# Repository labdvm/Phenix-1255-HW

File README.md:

<p align="center">
  <picture>
    <source media="(prefers-color-scheme: dark)" srcset="documentation/images/phenix-1255_logo_white.png">
    
  </picture>
</p>

<p align="center">
  <b>"Pi-less" SX1255 RF shield for the NXP FRDM-MCXN947</b><br>
  KiCad hardware design · separate RX/TX paths · 38.4 MHz TCXO · HS USB or Ethernet via the FRDM board
</p>

<p align="center">

</p>

<p align="center">
  <a href="#overview">Overview</a> ·
  <a href="#board-variants">Board variants</a> ·
  <a href="#features">Features</a> ·
  <a href="#preview">Preview</a> ·
  <a href="#documentation">Documentation</a> ·
  <a href="#repository-contents">Repository contents</a> ·
  <a href="#getting-started">Getting started</a> ·
  <a href="#license">License</a>
</p>

## Overview

Phenix-1255 is a shield board that pairs the popular **Semtech SX1255** RF transceiver with the
**NXP FRDM-MCXN947** development board — no Raspberry Pi required. The MCX N947 handles the
I/Q sample stream and talks to the host PC over **High-Speed USB** or **Ethernet**.

The project idea comes from **[DM5LF](https://github.com/w4tchd0g)**, who also writes the software. The hardware was designed by **[Z32IT](https://github.com/labdvm)**.

| | |
|---|---|
| 🧠 **Controller** | NXP FRDM-MCXN947 (plugs directly onto the shield headers) |
| 📡 **RF transceiver** | Semtech SX1255 (I/Q, 400–510 MHz) |
| ⏱️ **Reference clock** | 38.4 MHz TCXO, 0.5–1 ppm |
| 🔌 **Host link** | High-Speed USB 2.0 or Ethernet of the FRDM-MCXN947 |
| ⚡ **Power** | 5 V from the FRDM-MCXN947 (USB-C); PoE operation possible with a 48 V → 5 V USB-C PoE splitter |
| 📐 **PCB** | 118 × 55 mm, 2 layers, 1.2 mm thickness |

## Board variants

The repository contains two variants of revision V2. Both share the same board outline, headers,
power supply, user interface and RX path.

| Variant | Folder | Difference |
|---|---|---|
| **V2** | [`FRDM-SX1255/`](FRDM-SX1255) | SX1255 TX output → low-pass filter → U.FL |
| **V2 Plus** | [`FRDM-SX1255+/`](FRDM-SX1255+) | Additional **TX driver amplifier** (Qorvo TQP3M9036, U2) between the SX1255 and the low-pass filter, with a resistive π-attenuator (R29–R31) at its input. The amplifier runs from 5 V and is switched together with the PA via `~PA_EN`. |

## Features

- **Separate RX and TX paths** with U.FL connectors (*TX* J1, *RX* J2)
  - RX: SAW band-pass filter (Tai-Saw TA0655A, 430 MHz centre frequency, 2 MHz bandwidth) → LC matching → `RFI`
  - TX: `RFO_P` → low-pass filter (Mini-Circuits LFCN-490+) → U.FL; V2 Plus adds the TQP3M9036 driver amplifier
- **Switchable PA supply** – P-MOSFET (BSS84) controlled by `~PA_EN`, with a *bypass* solder jumper
- **Power supply** – resettable 500 mA fuse, TVS diode array (SP0502BAHT), ferrite bead and 3.3 V LDO (MCP1703)
- **User interface**
  - Three push buttons: *←*, *OK*, *→*
  - Socket for an I²C OLED display
  - Status LEDs: *PWR*, *Err*, *Warn*, *Good*

## Preview

### V2

| Top | Bottom |
|:---:|:---:|
|  |  |

### V2 Plus

| Top | Bottom |
|:---:|:---:|
|  |  |

The images are rendered from the `.kicad_pcb` files with the KiCad 3D renderer and show the fully
assembled board with a 0.96″ OLED module plugged into its socket, including the parts that are
marked *do not populate* in the layout (FRDM headers, OLED socket, SAW filter). After changing the
layout, run [`./scripts/render.sh`](scripts/render.sh) to update the images.

### 3D models

Every part on the board has a 3D model, so the board can be checked mechanically (e.g. for an
enclosure) and exported as STEP from KiCad. Most models come from the KiCad standard library
(`${KICAD10_3DMODEL_DIR}`); parts without a matching library model use these substitutes:

| Part | Footprint | 3D model | Source |
|---|---|---|---|
| FRDM headers J1, J2, J3, J4, J9, J12 | Samtec SSQ (FRDM template) | `PinHeader_2xNN_P2.54mm_Vertical` | KiCad library, mounted below the board |
| U.FL connectors *TX* / *RX* | `U.FL_Molex_MCRF_73412-0110_Vertical` | `U.FL_Hirose_U.FL-R-SMT-1_Vertical`, rotated 90° | KiCad library (no model for the Molex footprint) |
| Push buttons SW1–SW3 | `PTS647SK38SMTR2LFS` | `SW_SPST_PTS647Sx70` (7.0 mm actuator, as in the BOM) | KiCad library |
| SAW filter X1 (TA0655A) | `Filter_SAW-6_3.8x3.8mm` | [`3dmodels/TA0655A.stp`](FRDM-SX1255/3dmodels/TA0655A.stp) | Project file |
| TX amplifier U2 (V2 Plus) | `SON50P200X200X95-9N` | `VDFN-8-1EP_2x2mm_P0.5mm_EP0.9x1.7mm` | KiCad library |
| OLED display (plugged into J5) | `PinSocket_1x04_P2.54mm_Vertical` | [`3dmodels/OLED_0.96in_128x64_I2C.stp`](FRDM-SX1255/3dmodels/OLED_0.96in_128x64_I2C.stp) – 0.96″ 128×64 SSD1306 I²C module, as a second model on the socket | Project file |

Mounting holes and the *bypass* solder jumper need no model.

The shield is designed for the NXP FRDM-MCXN947 development board, see the
[NXP FRDM-MCXN947 product page](https://www.nxp.com/design/design-center/development-boards-and-designs/FRDM-MCXN947)
for photos, documentation and the board pinout.

## Documentation

| Document | Content |
|---|---|
| [Hardware](documentation/hardware.md) | Block overview, header pin assignment, PA supply and *bypass* jumper, power supply, V2 Plus amplifier |
| [Manufacturing and assembly](documentation/manufacturing.md) | PCB specification, production files, assembly notes, first power-up |

## Host PC requirements

| Component | Minimum |
|---|---|
| Interface | USB 2.0 (High-Speed) or Ethernet |
| CPU | Intel or AMD, 4 cores |
| RAM | 4 GB DDR3 |
| Storage | SSD |
| OS | Xubuntu x64 |

## Repository contents

Each board variant is a self-contained KiCad project in its own folder:

```
Phenix-1255-HW/
├── FRDM-SX1255/                      # V2
│   ├── FRDM-SX1255-V2.kicad_pro      # KiCad project – open this one
│   ├── FRDM-SX1255-V2.kicad_sch      # schematic
│   ├── FRDM-SX1255-V2.kicad_pcb      # PCB layout
│   ├── FRDM-SX1255-V2.pdf            # schematic as PDF
│   ├── FRDM-SX1255-V2.png / _b.png   # 2D board views (KiCad export)
│   ├── 3dmodels/                     # project-specific 3D models
│   └── Gerber and BOM/               # manufacturing data
│       ├── …_gerber.zip              # Gerber and drill files for PCB fabrication
│       ├── …_bom.csv                 # bill of materials (incl. DigiKey part numbers)
│       ├── …_positions.csv           # pick-and-place positions for assembly
│       └── …_netlist.ipc             # IPC-D-356 netlist for electrical testing
├── FRDM-SX1255+/                     # V2 Plus – same structure, files named "FRDM-SX1255+ V2.*"
├── documentation/                    # hardware and manufacturing documentation, images
└── scripts/render.sh                 # renders the PCB images (needs kicad-cli)
```

| Quick links | V2 | V2 Plus |
|---|---|---|
| Schematic (PDF) | [`FRDM-SX1255-V2.pdf`](FRDM-SX1255/FRDM-SX1255-V2.pdf) | [`FRDM-SX1255+ V2.pdf`](FRDM-SX1255+/FRDM-SX1255+%20V2.pdf) |
| Gerber | [`…_gerber.zip`](FRDM-SX1255/Gerber%20and%20BOM/FRDM-SX1255-V2.kicad_pcb_gerber.zip) | [`…_gerber.zip`](FRDM-SX1255+/Gerber%20and%20BOM/FRDM-SX1255+%20V2.kicad_pcb_gerber.zip) |
| BOM | [`…_bom.csv`](FRDM-SX1255/Gerber%20and%20BOM/FRDM-SX1255-V2.kicad_pcb_bom.csv) | [`…_bom.csv`](FRDM-SX1255+/Gerber%20and%20BOM/FRDM-SX1255+%20V2.kicad_pcb_bom.csv) |
| Positions | [`…_positions.csv`](FRDM-SX1255/Gerber%20and%20BOM/FRDM-SX1255-V2.kicad_pcb_positions.csv) | [`…_positions.csv`](FRDM-SX1255+/Gerber%20and%20BOM/FRDM-SX1255+%20V2.kicad_pcb_positions.csv) |

## Getting started

1. **Choose a variant** – V2, or V2 Plus if you want the additional TX driver amplifier.
2. **Order the PCB** – upload the Gerber ZIP to a PCB manufacturer of your choice
   (2 layers, **1.2 mm** board thickness). For assembly, provide the BOM and position files as well.
   Details: [Manufacturing and assembly](documentation/manufacturing.md).
3. **Assemble** the shield and plug it onto the FRDM-MCXN947.
4. **Connect antennas / RF cabling** to the U.FL connectors *TX* (J1) and *RX* (J2).
5. **Install the software** from [phenix-1255-sw](https://github.com/w4tchd0g/phenix-1255-sw).

## Related projects

- 💻 **Software:** [w4tchd0g/phenix-1255-sw](https://github.com/w4tchd0g/phenix-1255-sw)

## Credits

- **Idea & software:** DM5LF – [@w4tchd0g](https://github.com/w4tchd0g)
- **Hardware design:** Z32IT – [@labdvm](https://github.com/labdvm)

## License

Copyright © Z32IT 2026.

This source describes Open Hardware and is licensed under the **CERN-OHL-P v2**.

You may redistribute and modify this source and make products using it under the terms of the
[CERN-OHL-P v2](https://ohwr.org/cern_ohl_p_v2.txt). This source is distributed **WITHOUT ANY EXPRESS
OR IMPLIED WARRANTY, INCLUDING OF MERCHANTABILITY, SATISFACTORY QUALITY AND FITNESS FOR A PARTICULAR
PURPOSE**. Please see the CERN-OHL-P v2 for applicable conditions.

Source location: <https://github.com/labdvm/Phenix-1255-HW>

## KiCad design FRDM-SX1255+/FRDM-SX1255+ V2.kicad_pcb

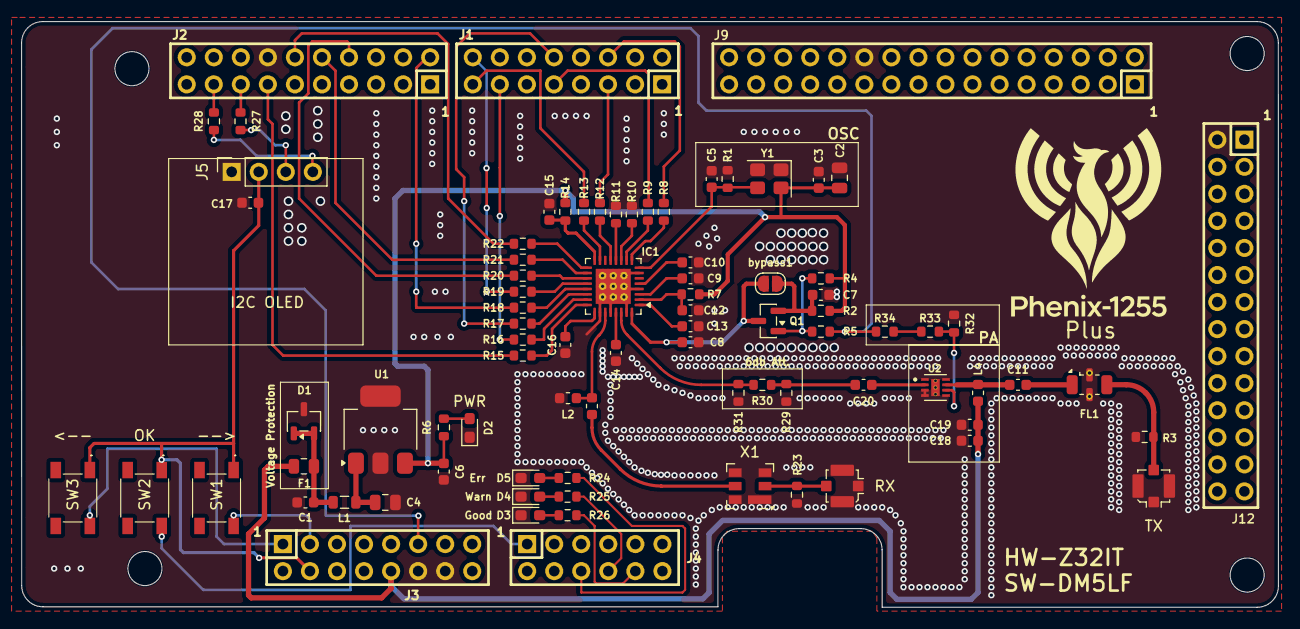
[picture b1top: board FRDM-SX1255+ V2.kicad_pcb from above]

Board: 2 copper layers, 118.0 x 55.0 mm, 88 parts (0 on the bottom side), 66 nets.

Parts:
C1, C6, C7, C12, C15, C18: 1u; C_0603_1608Metric
C2, C4: 22u; C_0805_2012Metric
C3, C8, C9, C10, C16, C17: 100n; C_0603_1608Metric
C5: 10p; C_0603_1608Metric
C11, C14, C19, C20: 100p; C_0603_1608Metric
C13: 10n; C_0603_1608Metric
D1: SP0502BAHT; SOT-23-3
D2: PWR; LED_0603_1608Metric_Pad1.05x0.95mm_HandSolder
D3: Good; LED_0603_1608Metric_Pad1.05x0.95mm_HandSolder
D4: Warn; LED_0603_1608Metric_Pad1.05x0.95mm_HandSolder
D5: Err; LED_0603_1608Metric_Pad1.05x0.95mm_HandSolder
F1: 500mA; Fuse_0805_2012Metric
FL1: LFCN-490; Filter_Mini-Circuits_FV1206
H1, H2, H3, H4: Mechanical_MountingHole; MOUNTINGHOLE_3.2MM_M3
IC1: SX1255; QFN-32-1EP_5x5mm_P0.5mm_EP3.3x3.3mm_ThermalVias
J1, J3: SSQ-108-03-T-D
J1#2: TX; U.FL_Molex_MCRF_73412-0110_Vertical
J2: RX; U.FL_Molex_MCRF_73412-0110_Vertical
J2#2: SSQ-110-03-T-D
J4: SSQ-106-03-T-D
J5: I2C OLED; PinSocket_1x04_P2.54mm_Vertical
J9: SSQ-116-03-T-D
J12: SSQ-114-03-T-D
L1: 600 ohm/100MHz; L_0805_2012Metric
L2: 82n; L_0603_1608Metric
L3: 39n; L_0603_1608Metric
L4: 68nH; L_0603_1608Metric
Q1: BSS84; SOT-23
R1, R4, R32: 10K; R_0603_1608Metric
R2, R7, R14, R34: 1R; R_0603_1608Metric
R3, R23: 1M; R_0603_1608Metric
R5, R10, R11, R12, R19, R20, R22: 330R; R_0603_1608Metric
R6: 3K3; R_0603_1608Metric
R8, R9, R13, R15, R16, R17, R18, R21, R27, R28: 33R; R_0603_1608Metric
R24, R25, R26: 1K5; R_0603_1608Metric
R29, R31: 150R; R_0603_1608Metric
R30: 36R; R_0603_1608Metric
R33: 33K; R_0603_1608Metric
SW1: -->; PTS647SK38SMTR2LFS
SW2: OK; PTS647SK38SMTR2LFS
SW3: <--; PTS647SK38SMTR2LFS
U1: MCP1703Ax-330xxDB; SOT-223-3_TabPin2
U2: TQP3M9036; SON50P200X200X95-9N
X1: TA0655A; Filter_SAW-6_3.8x3.8mm
Y1: 38.4MHz; Crystal_SMD_3225-4Pin_3.2x2.5mm
bypass1: Bypass; SolderJumper-2_P1.3mm_Open_RoundedPad1.0x1.5mm

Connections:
+3V3: C2.2, C3.1, C6.1, R2.2, R4.2, R6.2, R7.2, R14.1, U1.3 (VO), Y1.4 (VDD)
+5V0: C18.2, C19.1, F1.1, J3.10, L4.1
/+3.3V: C17.2, J3.4, J5.2, SW1.1, SW2.1, SW3.1
/BTN_LEFT: J3.1, SW3.2
/BTN_OK: J4.1, SW2.2
/BTN_RIGHT: J3.3, SW1.2
/CK_OUT: J1.9, R9.1
/DIO0: J2#2.2, R18.1
/DIO1: J1.10, R17.1
/DIO2: J1.13, R16.1
/DIO3: J2#2.13, R15.1
/I_IN: J1.5, R12.1
/I_OUT: J1.15, R13.1
/MISO: J2#2.10, R21.1
/MOSI: J2#2.8, R20.1
/NSS: J1.16, R19.1
/RF-out: C11.1, L4.2, U2.7
/RST: J1.6, R8.1
/SCK: J2#2.12, R22.1
/SCL_oled: J2#2.15, R27.2
/SDA_oled: J2#2.17, R28.2
/SX_CK_IN: IC1.11 (CK_IN), R10.2
/SX_CK_OUT: IC1.10 (CK_OUT), R9.2
/SX_DIO0: IC1.21 (DIO0), R18.2
/SX_DIO1: IC1.22 (DIO1), R17.2
/SX_DIO2: IC1.23 (DIO2), R16.2
/SX_DIO3: IC1.24 (DIO3), R15.2
/SX_I_IN: IC1.13 (I_IN), R12.2
/SX_I_OUT: IC1.15 (I_OUT), R13.2
/SX_MISO: IC1.18 (MISO), R21.2
/SX_MOSI: IC1.19 (MOSI), R20.2
/SX_NSS: IC1.20 (NSS), R19.2
/SX_Q_IN: IC1.12 (Q_IN), R11.2
/SX_RESET: IC1.9 (RESET), R8.2
/SX_RFI: IC1.27 (RFI), L2.2, L3.2
/SX_RFO_N: C14.2, IC1.29 (RFO_N)
/SX_RFO_P: IC1.30 (RFO_P), R30.1, R31.1
/SX_SCK: IC1.17 (SCK), R22.2
/SX_VBAT2: C15.1, IC1.16 (VBAT2), R14.2
/SX_VBAT3: C8.1, IC1.32 (VBAT3), Q1.3 (D), bypass1.2 (B)
/SX_VBATI: C12.1, IC1.2 (VBATI), R7.1
/SX_VR_ANA2: C16.2, IC1.25 (VR_ANA2)
/SX_VR_ANAI: C9.2, IC1.3 (VR_ANAI)
/SX_VR_DIG: C10.2, IC1.5 (VR_DIG)
/SX_VR_PA: C13.2, IC1.1 (VR_PA)
/TCXO: C5.1, IC1.8 (XTB), R1.1, Y1.3 (OUT)
/~PA_EN: J3.11, R5.1, R34.2
GND: C1.2, C2.1, C3.2, C4.2, C5.2, C6.2, C7.2, C8.2, C9.1, C10.1, C12.2, C13.1, C14.1, C15.2, C16.1, C17.1, C18.1, C19.2, D1.3 (A), D2.1 (K), D3.1 (K), D4.1 (K), D5.1 (K), FL1.2 (GND), FL1.4 (GND), IC1.4 (GND_1), IC1.7 (GND_2), IC1.26 (GND_3), IC1.28 (GND_4), IC1.31 (GND_5), IC1.33 (GND_6), J1#2.2 (Ext), J2.2 (Ext), J2#2.14, J3.12, J3.14, J5.1, J9.22, J12.2, L2.1, R1.2, R3.1, R10.1, R11.1, R23.1, R29.2, R31.2, R32.1, U1.2 (GND), U2.1, U2.3, U2.4, U2.5, U2.8, U2.9, U2.V1, U2.V2, U2.V3, X1.1 (GND), X1.3 (GND), X1.4 (GND), X1.6 (GND), Y1.1 (Tri-State), Y1.2 (GND)
unnamed: C1.1, D1.1 (K), D1.2 (K), F1.2, L1.1
unnamed: C20.1, R29.1, R30.2
unnamed: C20.2, U2.2
unnamed: D2.2 (A), R6.1
unnamed: D3.2 (A), R26.2
unnamed: D4.2 (A), R25.2
unnamed: D5.2 (A), R24.2
unnamed: C11.2, FL1.1 (IN)
unnamed: FL1.3 (OUT), J1#2.1 (In), R3.2
unnamed: J2.1 (In), R23.2, X1.2 (IN)
unnamed: J5.3, R27.1
unnamed: J5.4, R28.1
unnamed: Q1.1 (G), R4.1, R5.2
unnamed: C7.1, Q1.2 (S), R2.1, bypass1.1 (A)
unnamed: R32.2, R33.1, U2.6
unnamed: R33.2, R34.1
unnamed: C4.1, L1.2, U1.1 (VI)
unnamed: L3.1, X1.5 (OUT)

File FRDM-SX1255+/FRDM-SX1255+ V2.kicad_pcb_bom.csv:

Designator,Quantity,Value,Footprint,Package,MPN,DNP,Mount_Type,KiLib_Generator,Manufacturer,Manufacturer Product Number,Description,DigiKey Part Number,Sim.Pin,Aliexpress,TCXO-Footprints
"C1, C12, C15, C18, C6, C7",6,1u,C_0603_1608Metric,,311-3484-1-ND,,smt,SMD_2terminal_chip_molded,YAGEO,CC0603JRX7R6BB105,,,,,
"C10, C16, C17, C3, C8, C9",6,100n,C_0603_1608Metric,,720-1688-1-ND,,smt,SMD_2terminal_chip_molded,Vishay Vitramon,VJ0603Y104JXQPW1BC,,,,,
"C11, C14, C19, C20",4,100p,C_0603_1608Metric,,399-15348-1-ND,,smt,SMD_2terminal_chip_molded,KEMET,C0603C101J8GACTU,,,,,
C13,1,10n,C_0603_1608Metric,,399-C0603C103K8RACTUCT-ND,,smt,SMD_2terminal_chip_molded,KEMET,C0603C103K8RACTU,,,,,
"C2, C4",2,22u,C_0805_2012Metric,,1276-3148-1-ND,,smt,SMD_2terminal_chip_molded,Samsung Electro-Mechanics,CL31B226MPHNNNE,,,,,
C5,1,10p,C_0603_1608Metric,,399-14932-1-ND,,smt,SMD_2terminal_chip_molded,KEMET,C0603C100J8GACTU,,,,,
D1,1,SP0502BAHT,SOT-23-3,,,,smt,package/gullwing,Littelfuse Inc.,SP0502BAHTG,"TVS Diode Array, 5.5V Standoff, 2 Channels, SOT-23 package",F2714CT-ND,,,
D2,1,PWR,LED_0603_1608Metric_Pad1.05x0.95mm_HandSolder,,160-LTST-T180UWETCT-ND,,smt,SMD_2terminal_chip_molded,Lite-On Inc.,LTST-T180UWET,"Light emitting diode, small symbol",,1=K 2=A,,
D3,1,Good,LED_0603_1608Metric_Pad1.05x0.95mm_HandSolder,,754-APT1608SGD3CT-ND,,smt,SMD_2terminal_chip_molded,Kingbright,APT1608SGD3,"Light emitting diode, small symbol",,1=K 2=A,,
D4,1,Warn,LED_0603_1608Metric_Pad1.05x0.95mm_HandSolder,,160-1437-1-ND,,smt,SMD_2terminal_chip_molded,Lite-On Inc.,LTST-C190KSKT,"Light emitting diode, small symbol",,1=K 2=A,,
D5,1,Err,LED_0603_1608Metric_Pad1.05x0.95mm_HandSolder,,160-1479-1-ND,,smt,SMD_2terminal_chip_molded,Lite-On Inc.,LTST-S270KRKT,"Light emitting diode, small symbol",,1=K 2=A,,
F1,1,500mA,Fuse_0805_2012Metric,,,,smt,SMD_2terminal_chip_molded,Littelfuse Inc.,0805L050WR,"Resettable fuse, polymeric positive temperature coefficient, small symbol",F2772CT-ND,,,
FL1,1,LFCN-490,Filter_Mini-Circuits_FV1206,,3157-LFCN-490+CT-ND,,smt,,Mini-Circuits,LFCN-490+,,,,,
"H1, H2, H3, H4",4,Mechanical_MountingHole,MOUNTINGHOLE_3.2MM_M3,,,,tht,,,,,,,,
IC1,1,SX1255,QFN-32-1EP_5x5mm_P0.5mm_EP3.3x3.3mm_ThermalVias,,SX1255IWLTRTCT-ND,,smt,package/no_lead,Semtech Corporation,SX1255IWLTRT,,,,,
J1,1,TX,U.FL_Molex_MCRF_73412-0110_Vertical,,343-CONMHF1-SMD-G-TCT-ND,,smt,,TE Connectivity Linx,CONMHF1-SMD-G-T,,,,,
J2,1,RX,U.FL_Molex_MCRF_73412-0110_Vertical,,343-CONMHF1-SMD-G-TCT-ND,,smt,,TE Connectivity Linx,CONMHF1-SMD-G-T,,,,,
L1,1,600 ohm/100MHz,L_0805_2012Metric,,490-1046-1-ND,,smt,SMD_2terminal_chip_molded,Murata Electronics,BLM21BD601SN1D,FERRITE BEAD 600 OHM 0805 1LN,,,,
L2,1,82n,L_0603_1608Metric,,490-LQW18AS82NG00DCT-ND,,smt,SMD_2terminal_chip_molded,Murata Electronics,LQW18AS82NG00D,,,,,
L3,1,39n,L_0603_1608Metric,,490-LQW18AS39NG00DCT-ND,,smt,SMD_2terminal_chip_molded,Murata Electronics,LQW18AS39NG00D,,,,,
L4,1,68nH,L_0603_1608Metric,,490-1178-1-ND,,smt,SMD_2terminal_chip_molded,Murata Electronics,LQW18AN68NJ00D,,,,,
Q1,1,BSS84,SOT-23,,3372-BSS84TR-ND,,smt,package/gullwing,MDD,BSS84,,,,,
"R1, R32, R4",3,10K,R_0603_1608Metric,,541-10.0KHCT-ND,,smt,SMD_2terminal_chip_molded,Vishay Dale,CRCW060310K0FKEA,,,,,
"R10, R11, R12, R19, R20, R22, R5",7,330R,R_0603_1608Metric,,541-330HCT-ND,,smt,SMD_2terminal_chip_molded,Vishay Dale,CRCW0603330RFKEA,,,,,
"R13, R15, R16, R17, R18, R21, R27, R28, R8, R9",10,33R,R_0603_1608Metric,,541-33.0HCT-ND,,smt,SMD_2terminal_chip_molded,Vishay Dale,CRCW060333R0FKEA,,,,,
"R14, R2, R34, R7",4,1R,R_0603_1608Metric,,541-1.00HHCT-ND,,smt,SMD_2terminal_chip_molded,Vishay Dale,CRCW06031R00FKEA,,,,,
"R23, R3",2,1M,R_0603_1608Metric,,541-1.00MHCT-ND,,smt,SMD_2terminal_chip_molded,Vishay Dale,CRCW06031M00FKEA,,,,,
"R24, R25, R26",3,1K5,R_0603_1608Metric,,541-1.5KGCT-ND,,smt,SMD_2terminal_chip_molded,Vishay Dale,CRCW06031K50JNEA,,,,,
"R29, R31",2,150R,R_0603_1608Metric,,YAG1533CT-ND,,smt,SMD_2terminal_chip_molded,YAGEO,RT0603BRD07150RL,,,,,
R30,1,36R,R_0603_1608Metric,,13-RT0603BRC0736RLCT-ND,,smt,SMD_2terminal_chip_molded,YAGEO,RT0603BRC0736RL,,,,,
R33,1,33K,R_0603_1608Metric,,541-33.0KHCT-ND,,smt,SMD_2terminal_chip_molded,Vishay Dale,CRCW060333K0FKEA,,,,,
R6,1,3K3,R_0603_1608Metric,,541-3.30KHCT-ND,,smt,SMD_2terminal_chip_molded,Vishay Dale,CRCW06033K30FKEA,,,,,
SW1,1,-->,PTS647SK38SMTR2LFS,,,,smt,,C&K,PTS647SK70SMTR2N LFS,"Push button switch, generic, two pins",108-PTS647SK70SMTR2NLFSCT-ND,,,
SW2,1,OK,PTS647SK38SMTR2LFS,,,,smt,,C&K,PTS647SK70SMTR2N LFS,"Push button switch, generic, two pins",108-PTS647SK70SMTR2NLFSCT-ND,,,
SW3,1,<--,PTS647SK38SMTR2LFS,,,,smt,,C&K,PTS647SK70SMTR2N LFS,"Push button switch, generic, two pins",108-PTS647SK70SMTR2NLFSCT-ND,,,
U1,1,MCP1703Ax-330xxDB,SOT-223-3_TabPin2,,MCP1703T-3302E/DBCT-ND,,smt,,Microchip Technology,MCP1703T-3302E/DB,,,,,
U2,1,TQP3M9036,SON50P200X200X95-9N,,2312-TQP3M9036CT-ND,,smt,,Qorvo,TQP3M9036,,,,,
X1,1,TA0655A,Filter_SAW-6_3.8x3.8mm,,,,smt,,,,"Bandpass Filter, 430MHz, BW-4MHz",,,https://www.aliexpress.com/item/1005011831789075.html?pdp_ex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,
Y1,1,38.4MHz,Crystal_SMD_3225-4Pin_3.2x2.5mm,,114-TG2520SMN38.4000M-MCGNNM3CT-ND,,smt,crystal_resonator_oscillator,EPSON ,TG2520SMN 38.4000M-MCGNNM3,Clipped SW/0.5~1ppm,,,,3225 or 2510

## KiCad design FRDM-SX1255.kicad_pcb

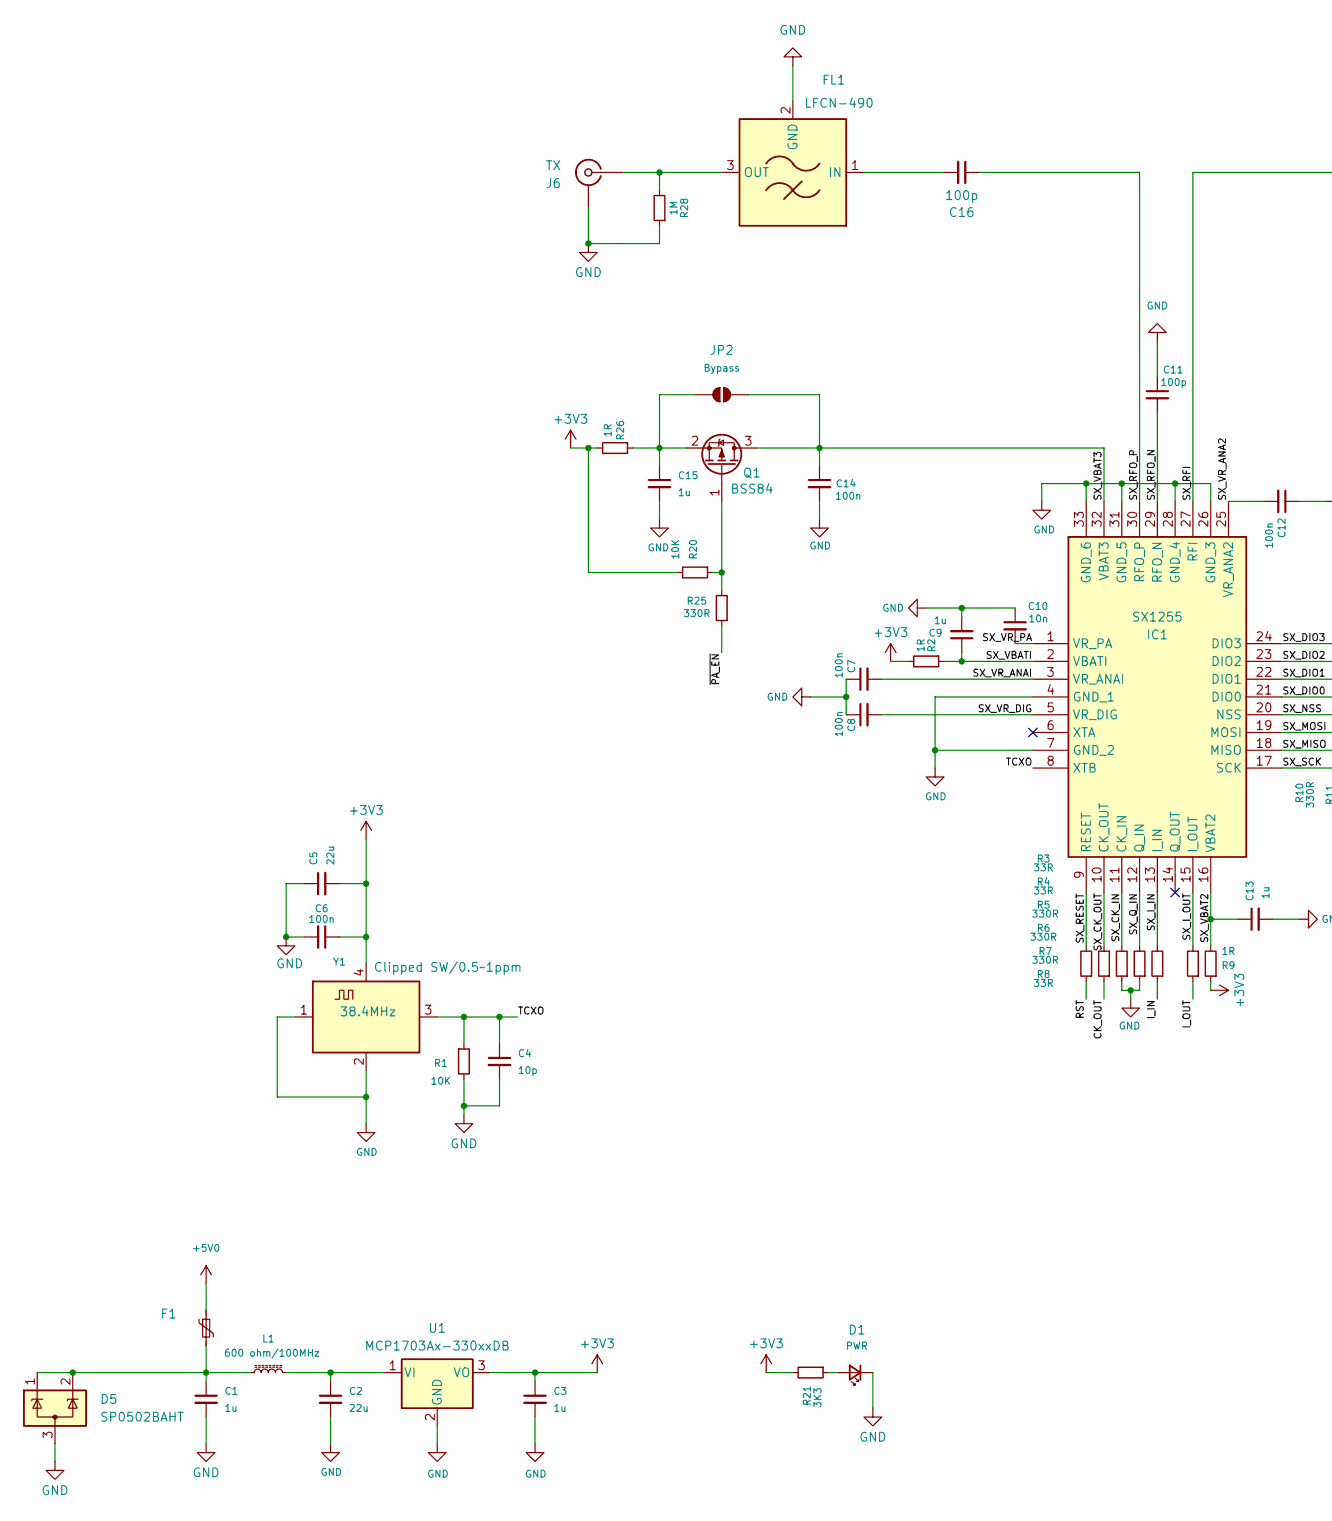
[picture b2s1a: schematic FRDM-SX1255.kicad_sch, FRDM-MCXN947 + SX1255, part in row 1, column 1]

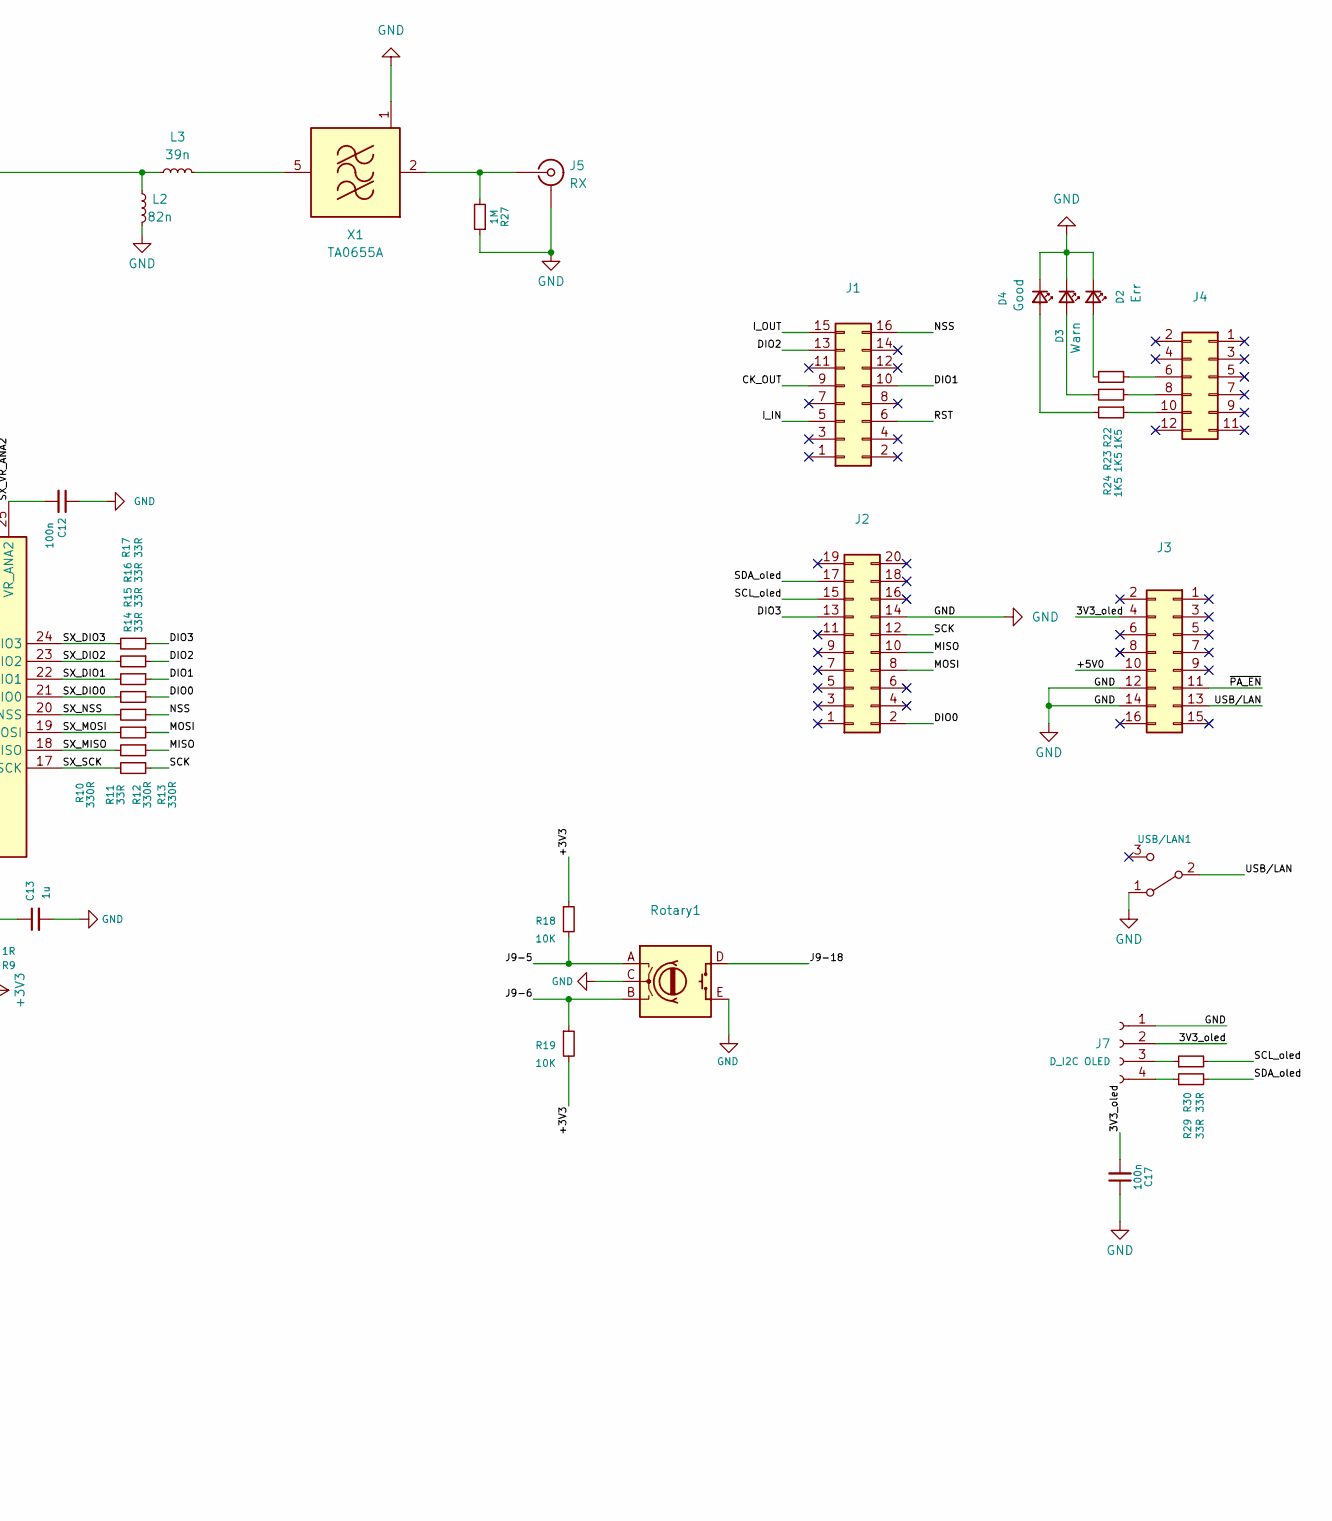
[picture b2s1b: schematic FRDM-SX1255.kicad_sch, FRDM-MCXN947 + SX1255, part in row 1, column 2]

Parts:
C1, C3, C9, C13, C15: 1u; C_0603_1608Metric; Part Number 311-3484-1-ND
C2, C5: 22u; C_0805_2012Metric; Part Number 1276-3148-1-ND
C4: 10p; C_0603_1608Metric; Part Number 399-14932-1-ND
C6, C7, C8, C12, C14, C17: 100n; C_0603_1608Metric; Part Number 720-1688-1-ND
C10: 10n; C_0603_1608Metric; Part Number 399-C0603C103K8RACTUCT-ND
C11, C16: 100p; C_0603_1608Metric; Part Number 399-15348-1-ND
D1: PWR; LED_0603_1608Metric_Pad1.05x0.95mm_HandSolder; Part Number 160-LTST-T180UWETCT-ND
D2: Err; LED_0603_1608Metric_Pad1.05x0.95mm_HandSolder; Part Number 160-1479-1-ND
D3: Warn; LED_0603_1608Metric_Pad1.05x0.95mm_HandSolder; Part Number 160-1437-1-ND
D4: Good; LED_0603_1608Metric_Pad1.05x0.95mm_HandSolder; Part Number 754-APT1608SGD3CT-ND
D5: SP0502BAHT; SOT-23-3; DigiKey Part Number F2714CT-ND
F1: 500mA; Fuse_0805_2012Metric; DigiKey Part Number F2772CT-ND
FL1: LFCN-490; Filter_Mini-Circuits_FV1206; Part Number 3157-LFCN-490+CT-ND
IC1: SX1255; QFN-32-1EP_5x5mm_P0.5mm_EP3.3x3.3mm_ThermalVias; Part Number SX1255IWLTRTCT-ND
J1, J3: PinHeader_2x08_P2.54mm_Vertical
J2: PinHeader_2x10_P2.54mm_Vertical
J4: PinHeader_2x06_P2.54mm_Vertical
J5: RX; U.FL_Molex_MCRF_73412-0110_Vertical; Part Number 343-CONMHF1-SMD-G-TCT-ND
J6: TX; U.FL_Molex_MCRF_73412-0110_Vertical; Part Number 343-CONMHF1-SMD-G-TCT-ND
J7: D_I2C OLED; PinSocket_1x04_P2.54mm_Vertical
JP2: Bypass; SolderJumper-2_P1.3mm_Open_RoundedPad1.0x1.5mm
L1: 600 ohm/100MHz; L_0805_2012Metric; Part Number 490-1046-1-ND
L2: 82n; L_0603_1608Metric; Part Number 490-LQW18AS82NG00DCT-ND
L3: 39n; L_0603_1608Metric; Part Number 490-LQW18AS39NG00DCT-ND
Q1: BSS84; SOT-23; Part Number 3372-BSS84TR-ND
R1, R18, R19, R20: 10K; R_0603_1608Metric; Part Number 541-10.0KHCT-ND
R2, R9, R26: 1R; R_0603_1608Metric; Part Number 541-1.00HHCT-ND
R3, R4, R8, R11, R14, R15, R16, R17, R29, R30: 33R; R_0603_1608Metric; Part Number 541-33.0HCT-ND
R5, R6, R7, R10, R12, R13, R25: 330R; R_0603_1608Metric; Part Number 541-330HCT-ND
R21: 3K3; R_0603_1608Metric; Part Number 541-3.30KHCT-ND
R22, R23, R24: 1K5; R_0603_1608Metric; Part Number 541-1.5KGCT-ND
R27, R28: 1M; R_0603_1608Metric; Part Number 541-1.00MHCT-ND
Rotary1: RotaryEncoder_Switch; RotaryEncoder_Alps_EC11E-Switch_Vertical_H20mm; Part Number 4809-EC11E09244AQ-ND
U1: MCP1703Ax-330xxDB; SOT-223-3_TabPin2; Part Number MCP1703T-3302E/DBCT-ND
USB/LAN1: SPDT_Slide_SMD_7.2x3.5mm; Slide_DPDT_SMD_7.2x3.5mm; Part Number 401-2013-1-ND
X1: TA0655A; Filter_SAW-6_3.8x3.8mm
Y1: 38.4MHz; Crystal_SMD_3225-4Pin_3.2x2.5mm; Part Number 114-TG2520SMN38.4000M-MCGNNM3CT-ND

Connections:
+3V3: C3.1, C5.2, C6.1, R2.2, R9.1, R18.1, R19.2, R20.2, R21.2, R26.2, U1.3 (VO), Y1.4 (VDD); also elsewhere on the board
+5V0: F1.1, J3.10
/3V3_oled: C17.2, J3.4, J7.2
/CK_OUT: J1.9, R4.1
/DIO0: J2.2, R14.1
/DIO1: J1.10, R15.1
/DIO2: J1.13, R16.1
/DIO3: J2.13, R17.1
/I_IN: J1.5, R7.1
/I_OUT: J1.15, R8.1
/J9-5: R18.2, Rotary1.A; also elsewhere on the board
/J9-6: R19.1, Rotary1.B; also elsewhere on the board
/J9-18: Rotary1.S1; also elsewhere on the board
/MISO: J2.10, R11.1
/MOSI: J2.8, R12.1
/NSS: J1.16, R13.1
/RST: J1.6, R3.1
/SCK: J2.12, R10.1
/SCL_oled: J2.15, R30.2
/SDA_oled: J2.17, R29.2
/SX_CK_IN: IC1.11 (CK_IN), R5.2
/SX_CK_OUT: IC1.10 (CK_OUT), R4.2
/SX_DIO0: IC1.21 (DIO0), R14.2
/SX_DIO1: IC1.22 (DIO1), R15.2
/SX_DIO2: IC1.23 (DIO2), R16.2
/SX_DIO3: IC1.24 (DIO3), R17.2
/SX_I_IN: IC1.13 (I_IN), R7.2
/SX_I_OUT: IC1.15 (I_OUT), R8.2
/SX_MISO: IC1.18 (MISO), R11.2
/SX_MOSI: IC1.19 (MOSI), R12.2
/SX_NSS: IC1.20 (NSS), R13.2
/SX_Q_IN: IC1.12 (Q_IN), R6.2
/SX_RESET: IC1.9 (RESET), R3.2
/SX_RFI: IC1.27 (RFI), L2.2, L3.2
/SX_RFO_N: C11.2, IC1.29 (RFO_N)
/SX_RFO_P: C16.1, IC1.30 (RFO_P)
/SX_SCK: IC1.17 (SCK), R10.2
/SX_VBAT2: C13.1, IC1.16 (VBAT2), R9.2
/SX_VBAT3: C14.1, IC1.32 (VBAT3), JP2.2 (B), Q1.3 (D)
/SX_VBATI: C9.1, IC1.2 (VBATI), R2.1
/SX_VR_ANA2: C12.2, IC1.25 (VR_ANA2)
/SX_VR_ANAI: C7.2, IC1.3 (VR_ANAI)
/SX_VR_DIG: C8.2, IC1.5 (VR_DIG)
/SX_VR_PA: C10.2, IC1.1 (VR_PA)
/TCXO: C4.1, IC1.8 (XTB), R1.1, Y1.3 (OUT)
/USB/LAN: J3.13, USB/LAN1.2 (B), USB/LAN1.5
/~PA_EN: J3.11, R25.1
GND: C1.2, C2.2, C3.2, C4.2, C5.1, C6.2, C7.1, C8.1, C9.2, C10.1, C11.1, C12.1, C13.2, C14.2, C15.2, C17.1, D1.1 (K), D2.1 (K), D3.1 (K), D4.1 (K), D5.3 (A), FL1.2 (GND), FL1.4 (GND), IC1.4 (GND_1), IC1.7 (GND_2), IC1.26 (GND_3), IC1.28 (GND_4), IC1.31 (GND_5), IC1.33 (GND_6), J2.14, J3.12, J3.14, J5.2 (Ext), J6.2 (Ext), J7.1, L2.1, R1.2, R5.1, R6.1, R27.1, R28.1, Rotary1.C, Rotary1.E, Rotary1.MP, Rotary1.S2, U1.2 (GND), USB/LAN1.1 (A), USB/LAN1.4, X1.1 (GND), X1.3 (GND), X1.4 (GND), X1.6 (GND), Y1.1 (Tri-State), Y1.2 (GND); also elsewhere on the board
unnamed: C1.1, D5.1 (K), D5.2 (K), F1.2, L1.1
unnamed: D1.2 (A), R21.1
unnamed: D2.2 (A), R22.2
unnamed: D3.2 (A), R23.2
unnamed: D4.2 (A), R24.2
unnamed: C16.2, FL1.1 (IN)
unnamed: FL1.3 (OUT), J6.1 (In), R28.2
unnamed: J4.6, R22.1
unnamed: J4.8, R23.1
unnamed: J4.10, R24.1
unnamed: J5.1 (In), R27.2, X1.2 (IN)
unnamed: J7.3, R30.1
unnamed: J7.4, R29.1
unnamed: C15.1, JP2.1 (A), Q1.2 (S), R26.1
unnamed: Q1.1 (G), R20.1, R25.2
unnamed: C2.1, L1.2, U1.1 (VI)
unnamed: L3.1, X1.5 (OUT)

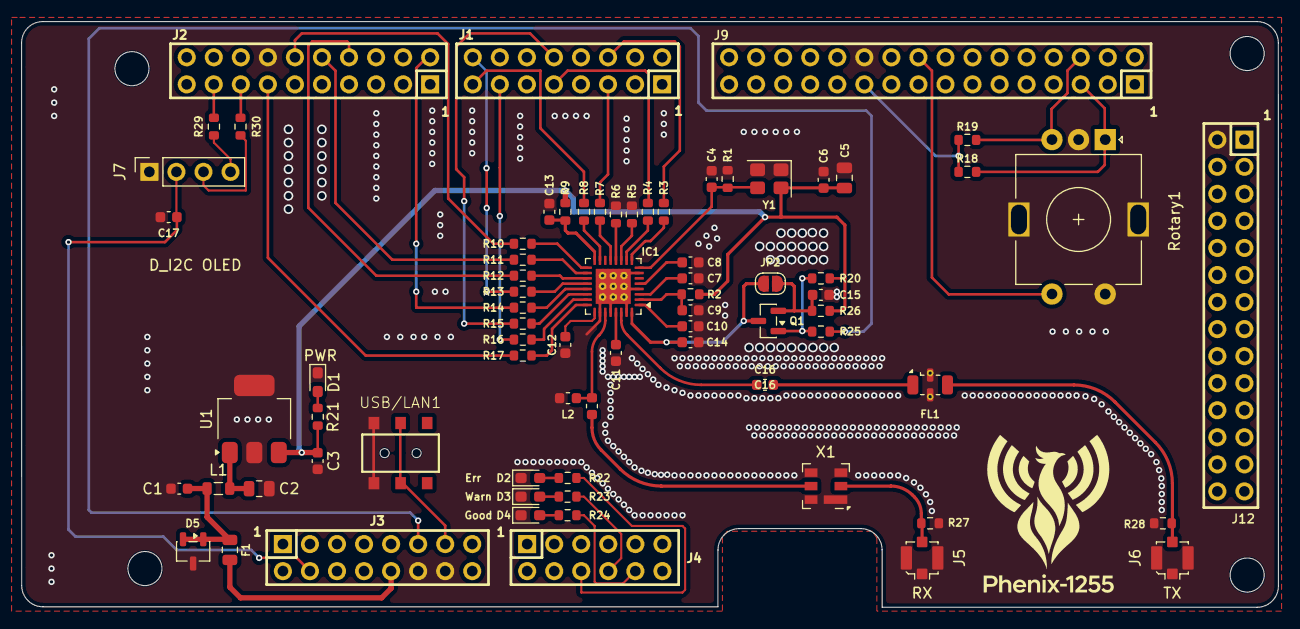
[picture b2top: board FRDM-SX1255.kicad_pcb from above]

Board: 2 copper layers, 118.0 x 55.0 mm, 78 parts (0 on the bottom side), 65 nets.

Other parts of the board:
H1, H2, H3, H4: Mechanical_MountingHole; MOUNTINGHOLE_3.2MM_M3
J9: SSQ-116-03-T-D
J12: SSQ-114-03-T-D

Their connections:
+3V3: J9.21; also elsewhere on the board
/J9-5: J9.5; also elsewhere on the board
/J9-6: J9.6; also elsewhere on the board
/J9-18: J9.18; also elsewhere on the board
GND: J9.22, J12.2; also elsewhere on the board

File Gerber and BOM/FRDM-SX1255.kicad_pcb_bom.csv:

Designator,Quantity,Value,Footprint,Package,MPN,DNP,Mount_Type,KiLib_Generator,Manufacturer,Manufacturer Product Number,Description,Sim.Pin,DigiKey Part Number,Aliexpress,TCXO-Footprints
"C1, C13, C15, C3, C9",5,1u,C_0603_1608Metric,,311-3484-1-ND,,smt,SMD_2terminal_chip_molded,YAGEO,CC0603JRX7R6BB105,,,,,
C10,1,10n,C_0603_1608Metric,,399-C0603C103K8RACTUCT-ND,,smt,SMD_2terminal_chip_molded,KEMET,C0603C103K8RACTU,,,,,
"C11, C16",2,100p,C_0603_1608Metric,,399-15348-1-ND,,smt,SMD_2terminal_chip_molded,KEMET,C0603C101J8GACTU,,,,,
"C12, C14, C17, C6, C7, C8",6,100n,C_0603_1608Metric,,720-1688-1-ND,,smt,SMD_2terminal_chip_molded,Vishay Vitramon,VJ0603Y104JXQPW1BC,,,,,
"C2, C5",2,22u,C_0805_2012Metric,,1276-3148-1-ND,,smt,SMD_2terminal_chip_molded,Samsung Electro-Mechanics,CL31B226MPHNNNE,,,,,
C4,1,10p,C_0603_1608Metric,,399-14932-1-ND,,smt,SMD_2terminal_chip_molded,KEMET,C0603C100J8GACTU,,,,,
D1,1,PWR,LED_0603_1608Metric_Pad1.05x0.95mm_HandSolder,,160-LTST-T180UWETCT-ND,,smt,SMD_2terminal_chip_molded,Lite-On Inc.,LTST-T180UWET,"Light emitting diode, small symbol",1=K 2=A,,,
D2,1,Err,LED_0603_1608Metric_Pad1.05x0.95mm_HandSolder,,160-1479-1-ND,,smt,SMD_2terminal_chip_molded,Lite-On Inc.,LTST-S270KRKT,"Light emitting diode, small symbol",1=K 2=A,,,
D3,1,Warn,LED_0603_1608Metric_Pad1.05x0.95mm_HandSolder,,160-1437-1-ND,,smt,SMD_2terminal_chip_molded,Lite-On Inc.,LTST-C190KSKT,"Light emitting diode, small symbol",1=K 2=A,,,
D4,1,Good,LED_0603_1608Metric_Pad1.05x0.95mm_HandSolder,,754-APT1608SGD3CT-ND,,smt,SMD_2terminal_chip_molded,Kingbright,APT1608SGD3,"Light emitting diode, small symbol",1=K 2=A,,,
D5,1,SP0502BAHT,SOT-23-3,,,,smt,package/gullwing,Littelfuse Inc.,SP0502BAHTG,"TVS Diode Array, 5.5V Standoff, 2 Channels, SOT-23 package",,F2714CT-ND,,
F1,1,500mA,Fuse_0805_2012Metric,,,,smt,SMD_2terminal_chip_molded,Littelfuse Inc.,0805L050WR,"Resettable fuse, polymeric positive temperature coefficient, small symbol",,F2772CT-ND,,
FL1,1,LFCN-490,Filter_Mini-Circuits_FV1206,,3157-LFCN-490+CT-ND,,smt,,Mini-Circuits,LFCN-490+,,,,,
"H1, H2, H3, H4",4,Mechanical_MountingHole,MOUNTINGHOLE_3.2MM_M3,,,,tht,,,,,,,,
IC1,1,SX1255,QFN-32-1EP_5x5mm_P0.5mm_EP3.3x3.3mm_ThermalVias,,SX1255IWLTRTCT-ND,,smt,package/no_lead,Semtech Corporation,SX1255IWLTRT,,,,,
J5,1,RX,U.FL_Molex_MCRF_73412-0110_Vertical,,343-CONMHF1-SMD-G-TCT-ND,,smt,,TE Connectivity Linx,CONMHF1-SMD-G-T,,,,,
J6,1,TX,U.FL_Molex_MCRF_73412-0110_Vertical,,343-CONMHF1-SMD-G-TCT-ND,,smt,,TE Connectivity Linx,CONMHF1-SMD-G-T,,,,,
L1,1,600 ohm/100MHz,L_0805_2012Metric,,490-1046-1-ND,,smt,SMD_2terminal_chip_molded,Murata Electronics,BLM21BD601SN1D,FERRITE BEAD 600 OHM 0805 1LN,,,,
L2,1,82n,L_0603_1608Metric,,490-LQW18AS82NG00DCT-ND,,smt,SMD_2terminal_chip_molded,Murata Electronics,LQW18AS82NG00D,,,,,
L3,1,39n,L_0603_1608Metric,,490-LQW18AS39NG00DCT-ND,,smt,SMD_2terminal_chip_molded,Murata Electronics,LQW18AS39NG00D,,,,,
Q1,1,BSS84,SOT-23,,3372-BSS84TR-ND,,smt,package/gullwing,MDD,BSS84,,,,,
"R1, R18, R19, R20",4,10K,R_0603_1608Metric,,541-10.0KHCT-ND,,smt,SMD_2terminal_chip_molded,Vishay Dale,CRCW060310K0FKEA,,,,,
"R10, R12, R13, R25, R5, R6, R7",7,330R,R_0603_1608Metric,,541-330HCT-ND,,smt,SMD_2terminal_chip_molded,Vishay Dale,CRCW0603330RFKEA,,,,,
"R11, R14, R15, R16, R17, R29, R3, R30, R4, R8",10,33R,R_0603_1608Metric,,541-33.0HCT-ND,,smt,SMD_2terminal_chip_molded,Vishay Dale,CRCW060333R0FKEA,,,,,
"R2, R26, R9",3,1R,R_0603_1608Metric,,541-1.00HHCT-ND,,smt,SMD_2terminal_chip_molded,Vishay Dale,CRCW06031R00FKEA,,,,,
R21,1,3K3,R_0603_1608Metric,,541-3.30KHCT-ND,,smt,SMD_2terminal_chip_molded,Vishay Dale,CRCW06033K30FKEA,,,,,
"R22, R23, R24",3,1K5,R_0603_1608Metric,,541-1.5KGCT-ND,,smt,SMD_2terminal_chip_molded,Vishay Dale,CRCW06031K50JNEA,,,,,
"R27, R28",2,1M,R_0603_1608Metric,,541-1.00MHCT-ND,,smt,SMD_2terminal_chip_molded,Vishay Dale,CRCW06031M00FKEA,,,,,
Rotary1,1,RotaryEncoder_Switch,RotaryEncoder_Alps_EC11E-Switch_Vertical_H20mm,,4809-EC11E09244AQ-ND,,tht,,Alps Alpine,EC11E09244AQ,"Rotary encoder, dual channel, incremental quadrate outputs, with switch",,,,
U1,1,MCP1703Ax-330xxDB,SOT-223-3_TabPin2,,MCP1703T-3302E/DBCT-ND,,smt,,Microchip Technology,MCP1703T-3302E/DB,,,,,
USB/LAN1,1,SPDT_Slide_SMD_7.2x3.5mm,Slide_DPDT_SMD_7.2x3.5mm,,401-2013-1-ND,,smt,,C&K,AYZ0202AGRLC,"Switch, single pole double throw",,,,
X1,1,TA0655A,Filter_SAW-6_3.8x3.8mm,,,,smt,,,,"Bandpass Filter, 430MHz, BW-4MHz",,,https://www.aliexpress.com/item/1005011831789075.html?pdp_ex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,
Y1,1,38.4MHz,Crystal_SMD_3225-4Pin_3.2x2.5mm,,114-TG2520SMN38.4000M-MCGNNM3CT-ND,,smt,crystal_resonator_oscillator,EPSON ,TG2520SMN 38.4000M-MCGNNM3,Clipped SW/0.5~1ppm,,,,3225 or 2510

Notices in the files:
README.md:
License: CERN-OHL-P v2
